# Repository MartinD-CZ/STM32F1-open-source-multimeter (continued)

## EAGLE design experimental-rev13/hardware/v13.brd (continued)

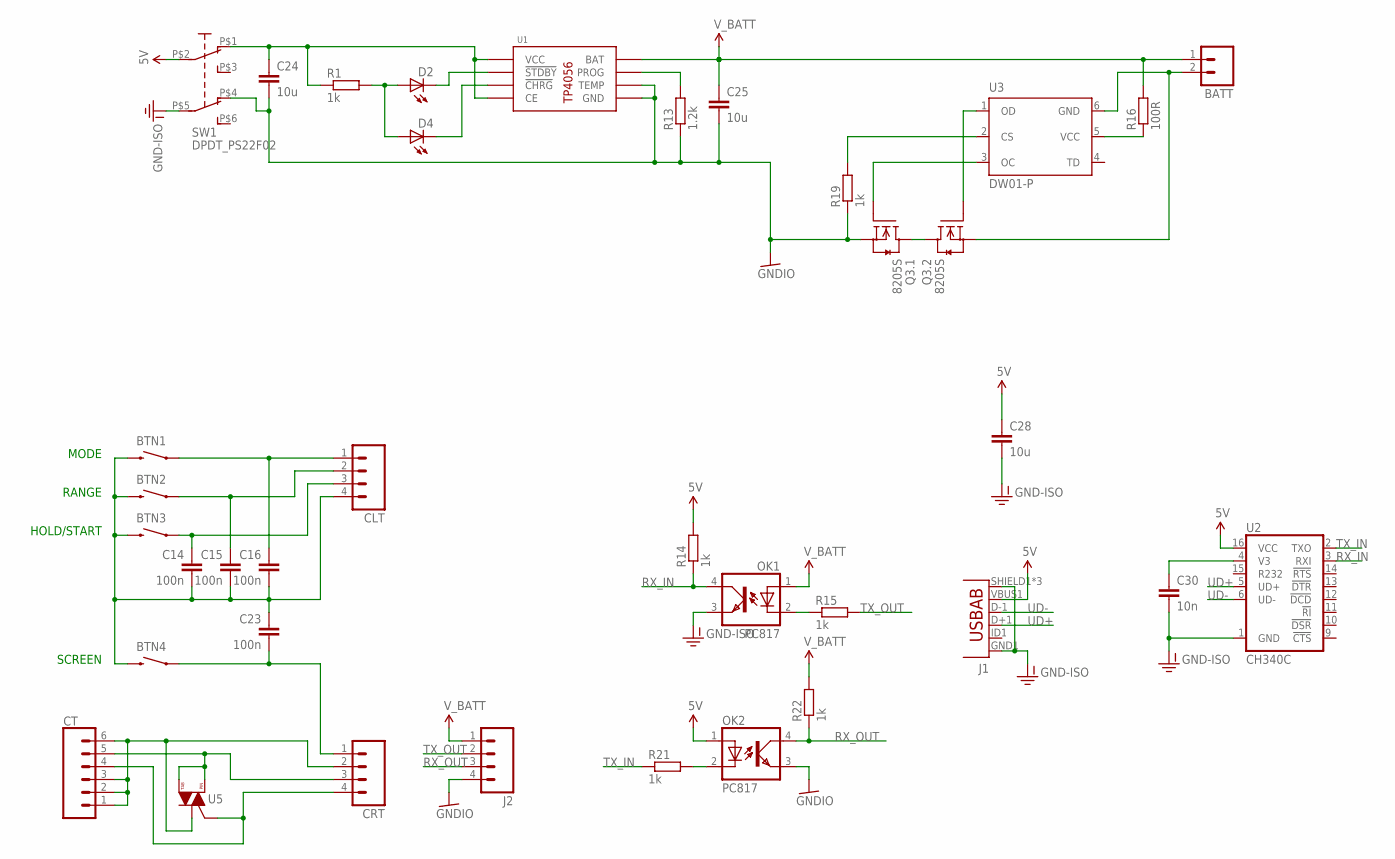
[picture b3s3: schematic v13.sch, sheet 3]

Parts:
BATT: M02PTH3; 1X02_LONGPADS
BTN1, BTN2, BTN3, BTN4: SWITCH-MOMENTARY-2PTH; TACTILE-PTH
C14, C15, C16, C23: 100n; C1206
C24, C25, C28: 10u; C1206
C30: 10n; C1206
CLT: M04PTH; 1X04@1
CRT: M04PTH; 1X04@1
CT: CONN_06NO_SILK_FEMALE_PTH; 1X06_NO_SILK
D2, D4: LEDCHIPLED_1206; CHIPLED_1206
J1: USB-ABCONN-11794; USB-AB-MICRO-SMD_V03
J2: M04PTH; 1X04@1
OK1, OK2: PC817; DIL04
Q3: 8205S; SSOT-6
R1, R14, R15, R19, R21, R22: 1k; R1206
R13: 1.2k; R1206
R16: 100R; R1206
SW1: DPDT_PS22F02; PS22_L02_DPDT_SW
U1: TP4056; SOP8
U2: CH340C; SO016
U3: DW01-P; SOT23-6L
U5: TRIAC-HPSMD; SOT223

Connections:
5V: C28.1, J1.VBUS1 (VBUS), OK2.1 (A), R14.2, SW1.P$2, U2.16 (VCC)
5V_ISO: C24.1, R1.1, SW1.P$1 (O), U1.4 (VCC), U1.8 (CE)
BTN1T: BTN1.1, C16.1, CLT.1
BTN2T: BTN2.1, C15.1, CLT.2
BTN3T: BTN3.1, C14.1, CLT.3
GND-ISO: C28.2, C30.2, J1.GND1 (GND), J1.SHIELD1 (SHIELD), J1.SHIELD2 (SHIELD), J1.SHIELD3 (SHIELD), OK1.3 (EMIT), SW1.P$5 (P1), U2.1 (GND)
GNDIO: C24.2, C25.2, J2.4, OK2.3 (EMIT), Q3.5 (S), R13.1, R19.1, SW1.P$4 (O1), U1.1 (TEMP), U1.3 (GND)
unnamed: D2.A, D4.A, R1.2
unnamed: BTN1.3 (2), BTN2.3 (2), BTN3.3 (2), BTN4.3 (2), C14.2, C15.2, C16.2, C23.1, CLT.4
unnamed: BTN4.1, C23.2, CRT.1
unnamed: D2.C, U1.6 (!STDBY)
unnamed: D4.C, U1.7 (!CHRG)
unnamed: R13.2, U1.2 (PROG)
unnamed: C30.1, U2.4 (V3)
unnamed: OK2.2 (C), R21.2
unnamed: OK1.2 (C), R15.1
unnamed: R16.1, U3.5 (VCC)
unnamed: BATT.2, Q3.2 (S), U3.6 (GND)
unnamed: Q3.4 (D), Q3.6 (D)
unnamed: Q3.3 (G), U3.1 (OD)
unnamed: Q3.1 (G), U3.3 (OC)
unnamed: R19.2, U3.2 (CS)
RX_IN: OK1.4 (COL), R14.1, U2.3 (RXI)
RX_OUT: J2.3, OK2.4 (COL), R22.1
TPA1_TOP: CRT.2, CT.1, CT.2, CT.3, CT.6, U5.1 (T1)
TPA2_TOP: CRT.3, CT.5, U5.2 (T2), U5.4 (T2)
TPA3_TOP: CRT.4, CT.4, U5.3 (G)
TX_IN: R21.1, U2.2 (TXO)
TX_OUT: J2.2, R15.2
UD+: J1.D+1 (D+), U2.5 (UD+)
UD-: J1.D-1 (D-), U2.6 (UD-)
V_BATT: BATT.1, C25.1, J2.1, OK1.1 (A), R16.2, R22.2, U1.5 (BAT); also elsewhere on the board

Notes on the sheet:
MODE
HOLD/START
RANGE
SCREEN

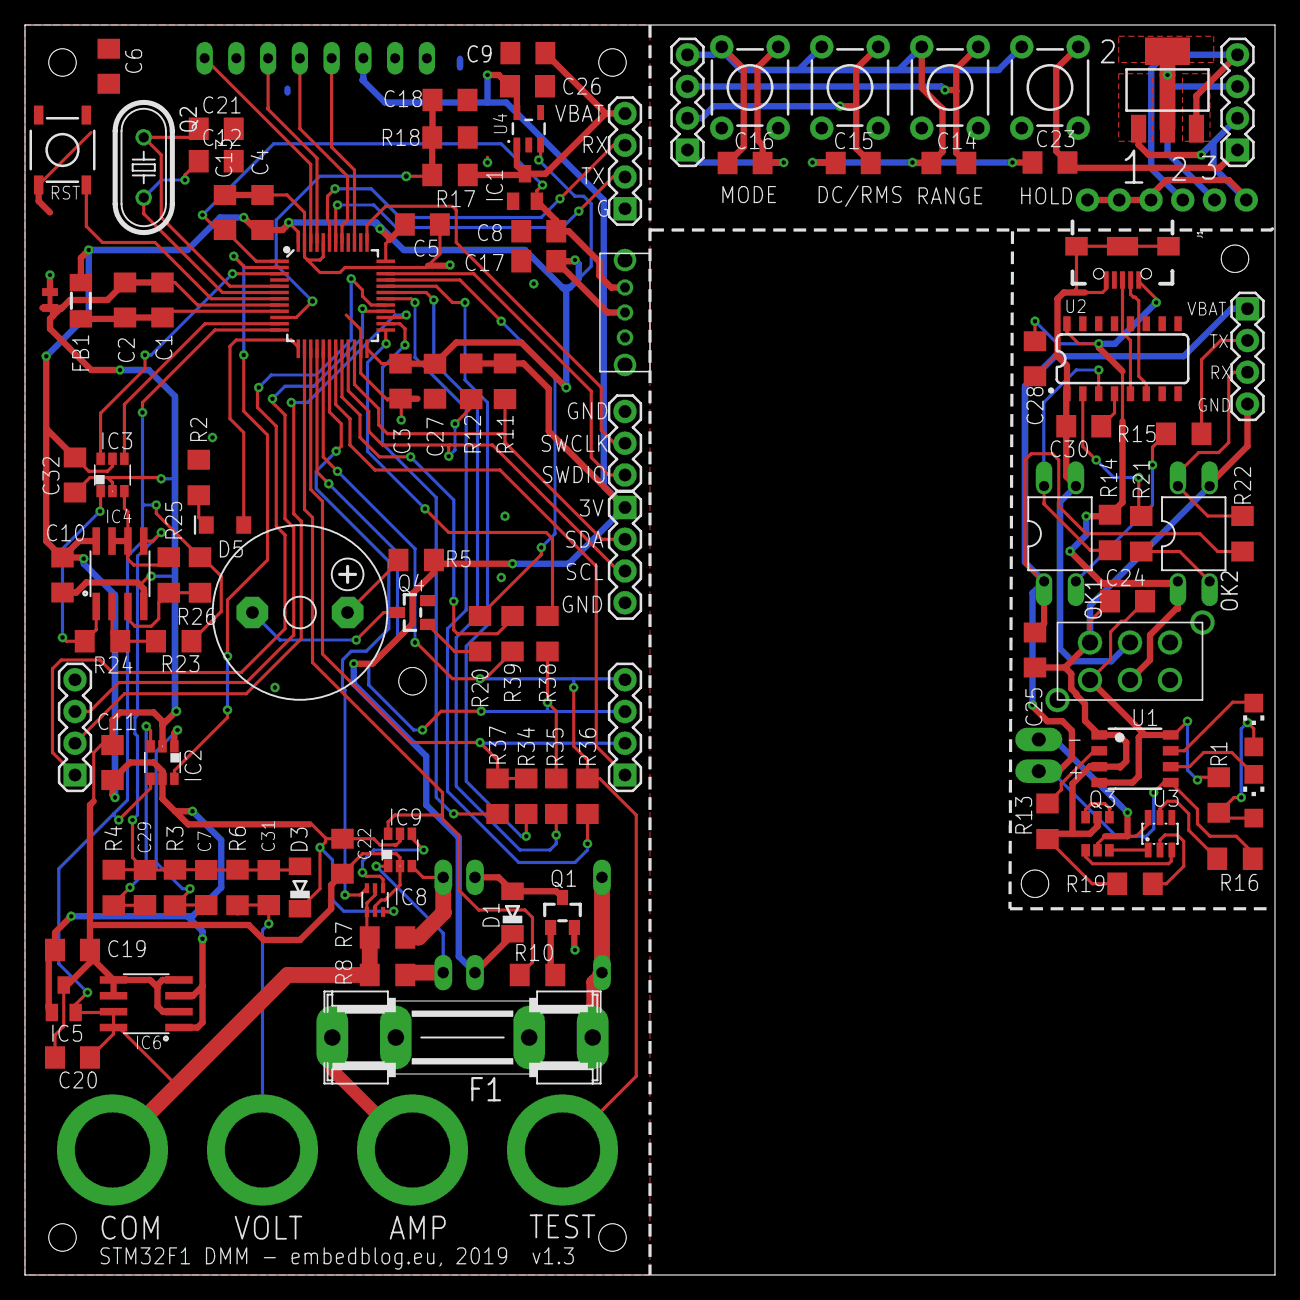
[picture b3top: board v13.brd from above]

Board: 2 copper layers, 100.0 x 100.0 mm, 116 parts (1 on the bottom side), 92 nets.

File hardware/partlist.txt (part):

Partlist

Exported from v12.sch at 27.05.2019 15:28

EAGLE Version 9.3.0 Copyright (c) 1988-2019 Autodesk, Inc.

Assembly variant: 

Part     Value                    Device                   Package              Library                    Sheet

BATT                              M02PTH3                  1X02_LONGPADS        SparkFun-Connectors        3
BTN1     SWITCH-MOMENTARY-2PTH    SWITCH-MOMENTARY-2PTH    TACTILE-PTH          SparkFun-Electromechanical 3
BTN2     SWITCH-MOMENTARY-2PTH    SWITCH-MOMENTARY-2PTH    TACTILE-PTH          SparkFun-Electromechanical 3
BTN3     SWITCH-MOMENTARY-2PTH    SWITCH-MOMENTARY-2PTH    TACTILE-PTH          SparkFun-Electromechanical 3
BTN4     SWITCH-MOMENTARY-2PTH    SWITCH-MOMENTARY-2PTH    TACTILE-PTH          SparkFun-Electromechanical 3
C1       100n                     C-EUC1206                C1206                resistor                   1
C2       1u                       C-EUC1206                C1206                resistor                   1
C3       100n                     C-EUC1206                C1206                resistor                   1
C4       100n                     C-EUC1206                C1206                resistor                   1
C5       100n                     C-EUC1206                C1206                resistor                   1
C6       100n                     C-EUC1206                C1206                resistor                   1
C7       1u                       C-EUC1206                C1206                resistor                   1
C8       1u                       C-EUC1206                C1206                resistor                   1
C9       22u                      C-EUC1206                C1206                resistor                   1
C10      100n                     CAP1206                  1206                 SparkFun-Passives          2
C11      100n                     CAP1206                  1206                 SparkFun-Passives          2
C13      100n                     C-EUC1206                C1206                resistor                   1
C14      100n                     C-EUC1206                C1206                resistor                   3
C15      100n                     C-EUC1206                C1206                resistor                   3
C16      100n                     C-EUC1206                C1206                resistor                   3
C17      22u                      C-EUC1206                C1206                resistor                   1
C18      DNP                      C-EUC1206                C1206                resistor                   1
C19      100n                     C-EUC1206                C1206                resistor                   2
C20      100n                     C-EUC1206                C1206                resistor                   2
C21      DNP                      C-EUC1206                C1206                resistor                   1
C22      DNP                      C-EUC1206                C1206                resistor                   1
C23      100n                     C-EUC1206                C1206                resistor                   3
C24      10u                      C-EUC1206                C1206                resistor                   3
C25      10u                      C-EUC1206                C1206                resistor                   3
C26      1u                       C-EUC1206                C1206                resistor                   1
C27      10u                      C-EUC1206                C1206                resistor                   1
C28      10u                      C-EUC1206                C1206                resistor                   3
C30      10n                      C-EUC1206                C1206                resistor                   3
CLB                               M04PTH                   1X04@1               SparkFun-Connectors        1
CLT                               M04PTH                   1X04@1               SparkFun-Connectors        3
CRB                               M04PTH                   1X04@1               SparkFun-Connectors        1
CRT                               M04PTH                   1X04@1               SparkFun-Connectors        3
CT                                M06SILK_FEMALE_PTH       1X06                 SparkFun-Connectors        2
D1                                DIODE-MINIMELF           MINIMELF             diode                      2
D2                                LEDCHIPLED_1206          CHIPLED_1206         led                        3
D3                                DIODE-MINIMELF           MINIMELF             diode                      2
D4                                LEDCHIPLED_1206          CHIPLED_1206         led                        3
D6                                DIODE-MINIMELF           MINIMELF             diode                      2
F1                                FUSEC                    1206                 m-pad-2.1                  2
FB1      1.8u                     FERRITE-BEADC            1206                 m-pad-2.1                  1
I2C                               M04PTH                   1X04@1               SparkFun-Connectors        1
IC1      MCP1700                  XC63FPM                  SOT23                v-reg                      1
IC2      741G3157DBVR             741G3157DBVR             DBV_R-PDSO-G6        74xx-little-de             2
IC4      MCP6072                  OPAMP-DUALU              SO08                 SparkFun-AnalogIC          2
IC5      REF3012                  MAX6520                  SOT23                maxim                      2
IC6      MCP1501                  MCP1501                  SO08                 custom                     2
IC7                               XC63FPM                  SOT23                v-reg                      1
J1                                USB-ABCONN-11794         USB-AB-MICRO-SMD_V03 SparkFun-Connectors        3
J2                                M04PTH                   1X04@1               SparkFun-Connectors        3
K2       FRS1B                    FRS1B                    FRS1B                relay                      2
LED1     RGBLED_CA-5MM            RGBLED_CA-5MM            LED5MMRGB            adafruit                   1
M1       5110_DISPLAY             5110_DISPLAY             5110_LAYOUT          custom                     1
OK1      PC817                    PC817                    DIL04                optocoupler                3
OK2      PC817                    PC817                    DIL04                optocoupler                3
PWR                               M04PTH                   1X04@1               SparkFun-Connectors        1
Q1       2N3904-MMBT              2N3904-MMBT              SOT23                m-pad-2.1                  2
Q2       DNP                      CRYSTALTC26H             TC26H                crystal                    1
Q3       8205S                    FDC6305N                 SSOT-6               m-pad-2.1                  3
Q4       2N3904-MMBT              2N3904-MMBT              SOT23                m-pad-2.1                  1
R1       1k                       R-EU_R1206               R1206                resistor                   3
R2       1k                       R-EU_R1206               R1206                resistor                   1
R3       250k                     R-EU_R1206               R1206                resistor                   2
R4       20k                      R-EU_R1206               R1206                resistor                   2
R5       100                      R-EU_R1206               R1206                resistor                   1
R6       1M                       R-EU_R1206               R1206                resistor                   2
R7       1                        R-EU_R1206               R1206                resistor                   2
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
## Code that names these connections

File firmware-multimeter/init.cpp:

/* ====================================================
 * STM32 OPEN SOURCE MULTIMETER
 * embedblog.eu/dmm
 * license: CC BY-NC-SA 4.0
 * ==================================================== */

#include "stm32f3xx.h"
#include "init.h"
#include "config.h"
#include "interrupt.h"

extern volatile uint8_t mode, rangeV;
extern volatile bool rangeI, aquisition;

void init_RCC(void)
{
	//init RCC to external crystal, PLL x9;
	RCC->CFGR |= RCC_CFGR_PLLSRC_HSE_PREDIV | RCC_CFGR_PLLMUL9 | RCC_CFGR_PPRE1_DIV2;
	RCC->CR |= RCC_CR_HSEON | RCC_CR_PLLON;
	FLASH->ACR |= FLASH_ACR_LATENCY_1;
	
	while (!(RCC->CR & RCC_CR_PLLRDY));
	
	RCC->CFGR |= RCC_CFGR_SW_PLL;
}

void init_GPIO(void)
{
	//enable GPIO clocks
	RCC->AHBENR |= RCC_AHBENR_GPIOAEN | RCC_AHBENR_GPIOBEN | RCC_AHBENR_GPIOCEN | RCC_AHBENR_GPIODEN | RCC_AHBENR_GPIOEEN| RCC_AHBENR_GPIOFEN;
	
	//enable OFSEL on PA12
	GPIOA->MODER |= GPIO_MODER_MODER12_0;
	GPIOA->OSPEEDR |= GPIO_OSPEEDER_OSPEEDR12;
	
	//enable buzzer on PA8
	GPIOA->MODER |= GPIO_MODER_MODER8_0;
	GPIOA->OSPEEDR |= GPIO_OSPEEDER_OSPEEDR8;
	
	//enable VSEL on PF6:7
	GPIOF->MODER |= GPIO_MODER_MODER6_0 | GPIO_MODER_MODER7_0;
	GPIOF->OSPEEDR |= GPIO_OSPEEDER_OSPEEDR6 | GPIO_OSPEEDER_OSPEEDR7;
	
	//enable ISEL on PB2
	GPIOB->MODER |= GPIO_MODER_MODER2_0;
	GPIOB->OSPEEDR |= GPIO_OSPEEDER_OSPEEDR2;
	
	//enable LED on PB6:7
	GPIOB->MODER |= GPIO_MODER_MODER6_0 | GPIO_MODER_MODER7_0;
	GPIOB->OSPEEDR |= GPIO_OSPEEDER_OSPEEDR6 | GPIO_OSPEEDER_OSPEEDR7;
	
	//se PA3:6, PB14:15 to high speed (used later for component testing/continuity)
	GPIOA->OSPEEDR |= GPIO_OSPEEDER_OSPEEDR3 | GPIO_OSPEEDER_OSPEEDR4 | GPIO_OSPEEDER_OSPEEDR5 | GPIO_OSPEEDER_OSPEEDR6;
	GPIOB->OSPEEDR |= GPIO_OSPEEDER_OSPEEDR14 | GPIO_OSPEEDER_OSPEEDR15;
}

void init_EXTI(void)
{
	//button pins (PC13:15, PA11) - inputs with pullups
	GPIOC->PUPDR |= GPIO_PUPDR_PUPDR13_0 | GPIO_PUPDR_PUPDR14_0 | GPIO_PUPDR_PUPDR15_0;
	GPIOA->PUPDR |= GPIO_PUPDR_PUPDR11_0;

	RCC->APB2ENR |= RCC_APB2ENR_SYSCFGEN;
	SYSCFG->EXTICR[2] |= SYSCFG_EXTICR3_EXTI11_PA;
	SYSCFG->EXTICR[3] |= SYSCFG_EXTICR4_EXTI13_PC | SYSCFG_EXTICR4_EXTI14_PC | SYSCFG_EXTICR4_EXTI15_PC;
	
	EXTI->IMR |= EXTI_IMR_MR11 | EXTI_IMR_MR13 | EXTI_IMR_MR14 | EXTI_IMR_MR15;
	EXTI->FTSR |= EXTI_FTSR_TR11 | EXTI_FTSR_TR13 | EXTI_FTSR_TR14 | EXTI_FTSR_TR15;
	
	NVIC_SetPriority(EXTI15_10_IRQn, 7);
	
	NVIC_EnableIRQ(EXTI15_10_IRQn);
}

void init_TIM3(void)			//used to update data
{
	//enable clock to Timer 3
	RCC->APB1ENR |= RCC_APB1ENR_TIM3EN;
	
	//set prescaler (7.2k - 1)
	TIM3->PSC = 7199;
	
	//set auto-reload register
	TIM3->ARR = (10000/SCREEN_UPDATE_RATE);
	
	//update registers
	TIM3->EGR |= TIM_EGR_UG;
	
	//zero the counter
	TIM3->CNT = 0x00;
	
	//enable interrupt on timer overflow (aka update event)
	TIM3->DIER |= TIM_DIER_UIE;
	
	NVIC_SetPriority(TIM3_IRQn, 1);
	NVIC_EnableIRQ(TIM3_IRQn);
	
	//enable timer
	TIM3->CR1 |= TIM_CR1_CEN;
}

void init_BKP(void)
{
	//disable write protection
	PWR->CR |= PWR_CR_DBP;
	
	if (RTC->BKP0R == DATA_SAVED)
	{
		mode = RTC->BKP1R;
		rangeV = RTC->BKP2R;
		rangeI = RTC->BKP3R;
		aquisition = RTC->BKP4R;
	}
	else
	{
		RTC->BKP0R = DATA_SAVED;
	}
	
	setVoltageRange();
	setCurrentRange();
	
	OFSEL_VREF2;
}

void init_TIM2(void)
{
	//enable clock to Timer 2
	RCC->APB1ENR |= RCC_APB1ENR_TIM2EN;
	
	//write into SMCR - prescaler /1; no filter; rising edge; clock mode 2
	TIM2->SMCR = TIM_SMCR_ECE;
	
	//enable counter
	TIM2->CR1 |= TIM_CR1_CEN;
}

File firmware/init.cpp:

//====================================================
// STM32 OPEN SOURCE MULTIMETER
// embedblog.eu/dmm
// CC BY-NC-SA 4.0
// ===================================================

#include "stm32f10x.h"
#include "init.h"
#include "defines.h"

void init_rcc(void)
{
	//CLOCK INIT - RUNNING FROM 8 MHz INTERNAL RC OSCILLATOR, CORE FREQUENCY 64 MHz	

	RCC->CFGR |= RCC_CFGR_PPRE1_DIV2 | RCC_CFGR_PLLMULL16 | RCC_CFGR_PLLSRC_HSI_Div2 | RCC_CFGR_PPRE1_DIV2;
	RCC->CR |= RCC_CR_PLLON;
	RCC->CFGR |= RCC_CFGR_SW_PLL;
	
	//set flash latency
	FLASH->ACR |= FLASH_ACR_LATENCY_2;
}

void init_gpio(void)
{
	//enable GPIO clocks
	RCC->APB2ENR |= RCC_APB2ENR_IOPAEN | RCC_APB2ENR_IOPBEN | RCC_APB2ENR_IOPCEN | RCC_APB2ENR_IOPDEN;
	
	//enable AFIO and disable JTAG
	RCC->APB2ENR |= RCC_APB2ENR_AFIOEN;
	AFIO->MAPR = (0x2 << 24);
	
	//remap PD0 and PD1
	AFIO->MAPR |= AFIO_MAPR_PD01_REMAP;
	
	//enable PD0:1 as outputs
	GPIOD->CRL |= GPIO_CRL_MODE0 | GPIO_CRL_MODE1;
	GPIOD->CRL &=~(GPIO_CRL_CNF0_0 | GPIO_CRL_CNF1_0);
	
	//enable voltage range switch on PA3
	GPIOA->CRL |= GPIO_CRL_MODE3;
	GPIOA->CRL &=~GPIO_CRL_CNF3_0;
	
	//enable current range switch on PA4
	GPIOA->CRL |= GPIO_CRL_MODE4;
	GPIOA->CRL &=~GPIO_CRL_CNF4_0;
	
	//enable buzzer on PA12
	GPIOA->CRH |= GPIO_CRH_MODE12;
	GPIOA->CRH &=~GPIO_CRH_CNF12_0;
}

void init_exti(void)
{
	//button pins (PA8, PB1, PB14, PB15) - inputs with pullups
	GPIOA->CRH &=~ GPIO_CRH_CNF8_0;
	GPIOA->CRH |= GPIO_CRH_CNF8_1;
	GPIOA->ODR |= GPIO_ODR_ODR8;
	
	GPIOB->CRL &=~ GPIO_CRL_CNF1_0;
	GPIOB->CRL |= GPIO_CRL_CNF1_1;
	GPIOB->ODR |= GPIO_ODR_ODR1;
	
	GPIOB->CRH &=~ GPIO_CRH_CNF14_0;
	GPIOB->CRH |= GPIO_CRH_CNF14_1;
	GPIOB->ODR |= GPIO_ODR_ODR14;
	
	GPIOB->CRH &=~ GPIO_CRH_CNF15_0;
	GPIOB->CRH |= GPIO_CRH_CNF15_1;
	GPIOB->ODR |= GPIO_ODR_ODR15;
	
	//reset MODE
	//GPIOC->CRH &=~(GPIO_CRH_MODE13_0 | GPIO_CRH_MODE14_0 | GPIO_CRH_MODE15_0);
	
	AFIO->EXTICR[2] |= AFIO_EXTICR3_EXTI8_PA;
	AFIO->EXTICR[0] |= AFIO_EXTICR1_EXTI1_PB;
	AFIO->EXTICR[3] |= AFIO_EXTICR4_EXTI14_PB | AFIO_EXTICR4_EXTI15_PB;
	
	EXTI->IMR |= EXTI_IMR_MR1 | EXTI_IMR_MR8 | EXTI_IMR_MR14 | EXTI_IMR_MR15;
	EXTI->FTSR |= EXTI_FTSR_TR1 | EXTI_FTSR_TR8 | EXTI_FTSR_TR14 | EXTI_FTSR_TR15;
	
	//NVIC_SetPriorityGrouping(3);
	
	NVIC_SetPriority(EXTI1_IRQn, 7);
	NVIC_SetPriority(EXTI9_5_IRQn, 7);
	NVIC_SetPriority(EXTI15_10_IRQn, 7);
	
	NVIC_EnableIRQ(EXTI1_IRQn);
	NVIC_EnableIRQ(EXTI9_5_IRQn);
	NVIC_EnableIRQ(EXTI15_10_IRQn);
}

uint8_t init_rtc(void)
{
	RCC->APB1ENR |= RCC_APB1ENR_BKPEN | RCC_APB1ENR_PWREN;
	
	PWR->CR |= PWR_CR_DBP;
	
	if (BKP->DR1 == DATA_SAVED)
		return ((uint8_t)BKP->DR2);
	else
		BKP->DR1 = DATA_SAVED;
	
	return 0;
}

void init_timer2(void)
{
	//enable clock to Timer 2
	RCC->APB1ENR |= RCC_APB1ENR_TIM2EN;
	
	//set prescaler (63k + 1)
	TIM2->PSC = 63999;
	
	//update registers
	TIM2->EGR |= TIM_EGR_UG;
	
	//zero the counter
	TIM2->CNT = 0x00;
	
	//enable interrupt on CC1
	TIM2->DIER |= TIM_DIER_CC1IE;
	
	TIM2->CCR1 = (1000/SCREEN_UPDATE_RATE);
	
	NVIC_SetPriority(TIM2_IRQn, 1);
	NVIC_EnableIRQ(TIM2_IRQn);
	
	//enable timer
	TIM2->CR1 |= TIM_CR1_CEN;
}

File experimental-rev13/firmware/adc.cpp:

//====================================================
// STM32 OPEN SOURCE MULTIMETER
// embedblog.eu/dmm
// CC BY-NC 4.0
// ===================================================

#include "stm32f10x.h"
#include "adc.h"
#include "defines.h"

volatile uint16_t adc_data[12];

void adc1_init(void)
{
	//ADC clock prescaler
	RCC->CFGR |= RCC_CFGR_ADCPRE_DIV6;
	
	//enable ADC clock
	RCC->APB2ENR |= RCC_APB2ENR_ADC1EN;
	
	//pins PA1:2 as analog
	GPIOA->CRL &=~(GPIO_CRL_CNF1_0 | GPIO_CRL_CNF2_0);
	
	//pin PB0 as analog
	GPIOB->CRL &=~GPIO_CRL_CNF0_0;
	
	//sample time 28.5 cycles for channels 1, 2
	//ADC1->SMPR2 |= (5 << 0) | (5 << 3) | (5 << 6);
	//ADC1->SMPR2 |= (4 << 0) | (4 << 3) | (4 << 6);
	ADC1->SMPR2 |= (3 << 3) | (3 << 6) | (3 << 24);
	
	//enable continuous mode
	ADC1->CR2 |= ADC_CR2_CONT;
	
	//enable scan mode
	ADC1->CR1 |= ADC_CR1_SCAN;
	
	//enable DMA mode
	ADC1->CR2 |= ADC_CR2_DMA;
	
	//convert CH1, CH2 and CH8
	ADC1->SQR1 = (11 << 20);
	ADC1->SQR3 = (2 << 0) | (1 << 5) | (8 << 10) | (2 << 15) | (1 << 20) | (8 << 25);
	ADC1->SQR2 = (2 << 0) | (1 << 5) | (8 << 10) | (2 << 15) | (1 << 20) | (8 << 25);
	
	//DMA SETUP
	//enable clock for DMA
	RCC->AHBENR |= RCC_AHBENR_DMA1EN;
	
	//setup DMA1
	//set priority to very high
	DMA1_Channel1->CCR |= DMA_CCR1_PL_0 | DMA_CCR1_PL_1;
	
	//enable DMA1 TC INT
	DMA1_Channel1->CCR |= DMA_CCR1_TCIE;
	
	//set memory size to 16 bits
	DMA1_Channel1->CCR |= DMA_CCR1_MSIZE_0;
	
	//set peripheral size to 16 bits
	DMA1_Channel1->CCR |= DMA_CCR1_PSIZE_0;
	
	//increment memory
	DMA1_Channel1->CCR |= DMA_CCR1_MINC;
	
	//set circular mode
	DMA1_Channel1->CCR |= DMA_CCR1_CIRC;
	
	//12 transfers
	DMA1_Channel1->CNDTR = 12;
	
	//peripheral (source) address
	DMA1_Channel1->CPAR = (uint32_t)(&(ADC1->DR));
	
	//memory (destination) address
	DMA1_Channel1->CMAR = (uint32_t)(adc_data);
	
	NVIC_SetPriority(DMA1_Channel1_IRQn, 2);
}

void adc1_start(void)
{	
	NVIC_EnableIRQ(DMA1_Channel1_IRQn);
	
	//set DMA to 12 transfers
	DMA1_Channel1->CNDTR = 12;
	
	//start DMA
	DMA1_Channel1->CCR |= DMA_CCR1_EN;
	
	//wake up ADC
	ADC1->CR2 |= ADC_CR2_ADON;
	
	//clear ADC calibration
	ADC1->CR2 |= ADC_CR2_RSTCAL;
	
	//launch ADC calibration
	ADC1->CR2 |= ADC_CR2_CAL;
	
	while ((ADC1->CR2 & ADC_CR2_CAL) == ADC_CR2_CAL);
	
	//second ADON write = start conversion
	ADC1->CR2 |= ADC_CR2_ADON;
}

void adc1_stop(void)
{
	//disable ADC
	ADC1->CR2 &=~ADC_CR2_ADON;
	
	NVIC_DisableIRQ(DMA1_Channel1_IRQn);
	
	//disable DMA
	DMA1_Channel1->CCR &=~DMA_CCR1_EN;
}

void adc2_init(void)
{
	//enable ADC clock
	RCC->APB2ENR |= RCC_APB2ENR_ADC2EN;
	
	//pins PA0, PA5:7 as analog
	GPIOA->CRL &=~(GPIO_CRL_CNF0_0 | GPIO_CRL_CNF5_0 | GPIO_CRL_CNF6_0 | GPIO_CRL_CNF7_0);
	
	//sample time 239.5 cycles for channels 5, 6, 7, 8
	ADC2->SMPR2 |= (7 << 15) | (7 << 18) | (7 << 21) | (7 << 0);
	
	//wake up ADC
	ADC2->CR2 |= ADC_CR2_ADON;
	
	//clear ADC calibration
	ADC2->CR2 |= ADC_CR2_RSTCAL;
	
	//launch ADC calibration
	ADC2->CR2 |= ADC_CR2_CAL;
	
	//wait for calibration complete
	while ((ADC2->CR2 & ADC_CR2_CAL) == ADC_CR2_CAL);
}

uint16_t adc2_getReading(uint8_t channel, uint8_t oversamplig)
{
	uint16_t data = 0;
	
	switch(channel)
	{
		case VBAT: ADC2->SQR3 = (0 << 0); break;
		case TP1: ADC2->SQR3 = (5 << 0); break;
		case TP2: ADC2->SQR3 = (6 << 0); break;
		case TP3: ADC2->SQR3 = (7 << 0); break;
	}
	
	for (uint8_t i = 0; i < oversamplig; i ++)
	{
		ADC2->CR2 |= ADC_CR2_ADON;		//second ADON write = start conversion
		while ((ADC2->SR & ADC_SR_EOC) != ADC_SR_EOC);		//wait for conversion complete
		data += ADC2->DR;							//get data
	}
	
	return (data / oversamplig);
}

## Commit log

2019-05-27 V1.2b
    initial release
2019-06-26 added experimental rev 1.3
    see my blog for more info
2019-06-26 fixed readme error
2019-09-30 rev 1.5
    ton of new features, see the blog
2019-10-02 updated files for 3D printing
2021-01-06 Create LICENSE
